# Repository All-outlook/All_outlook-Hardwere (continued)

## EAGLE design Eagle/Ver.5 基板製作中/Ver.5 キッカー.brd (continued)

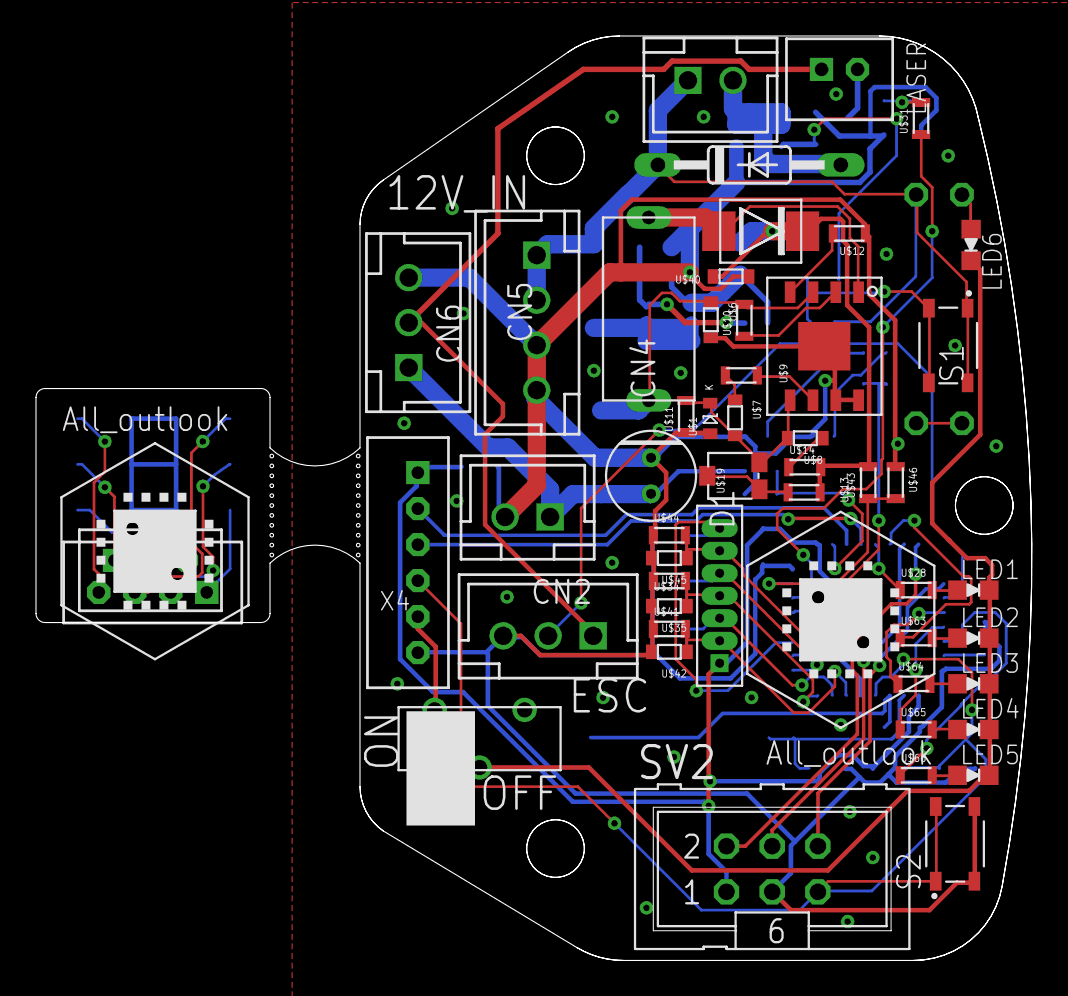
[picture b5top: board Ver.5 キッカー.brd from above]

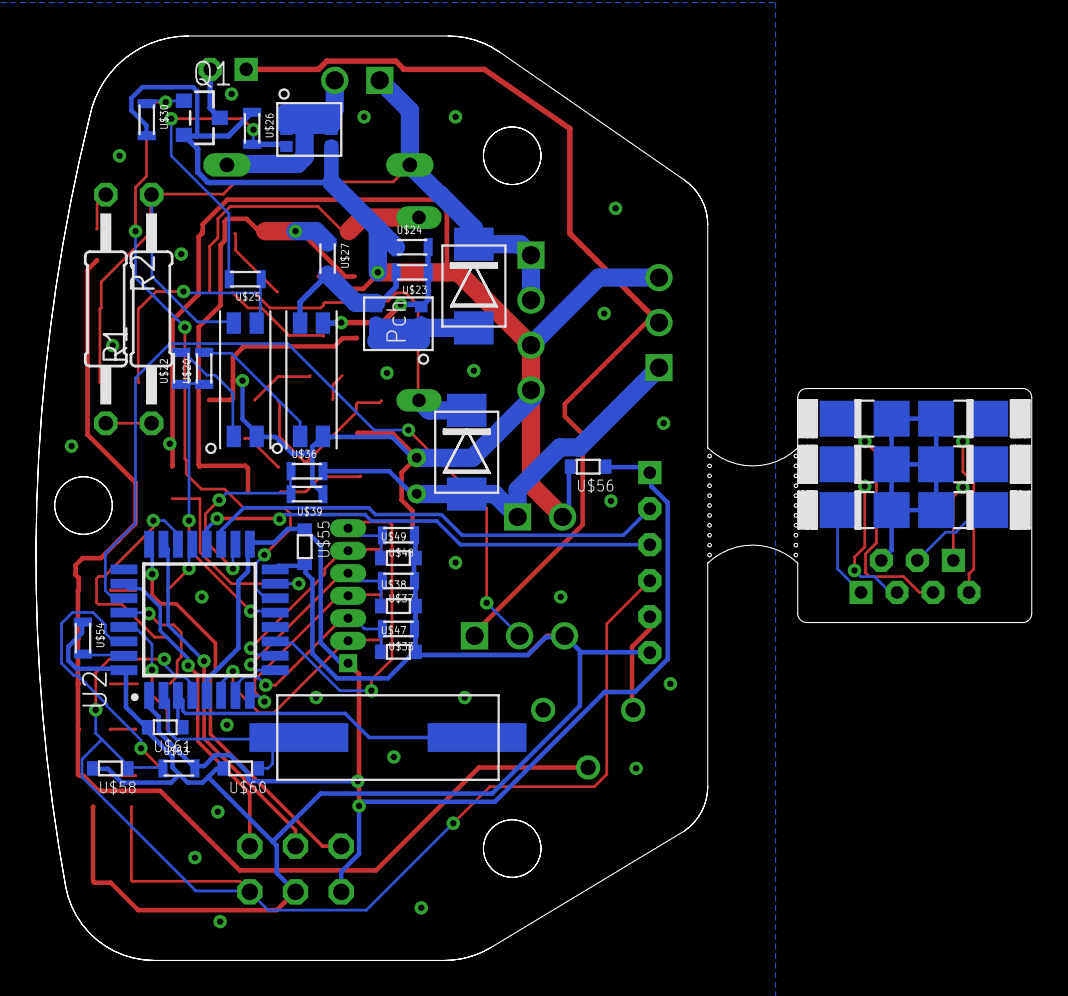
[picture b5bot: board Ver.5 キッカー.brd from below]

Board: 2 copper layers, 55.3 x 51.4 mm, 93 parts (34 on the bottom side), 66 nets.

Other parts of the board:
U$32: ALL

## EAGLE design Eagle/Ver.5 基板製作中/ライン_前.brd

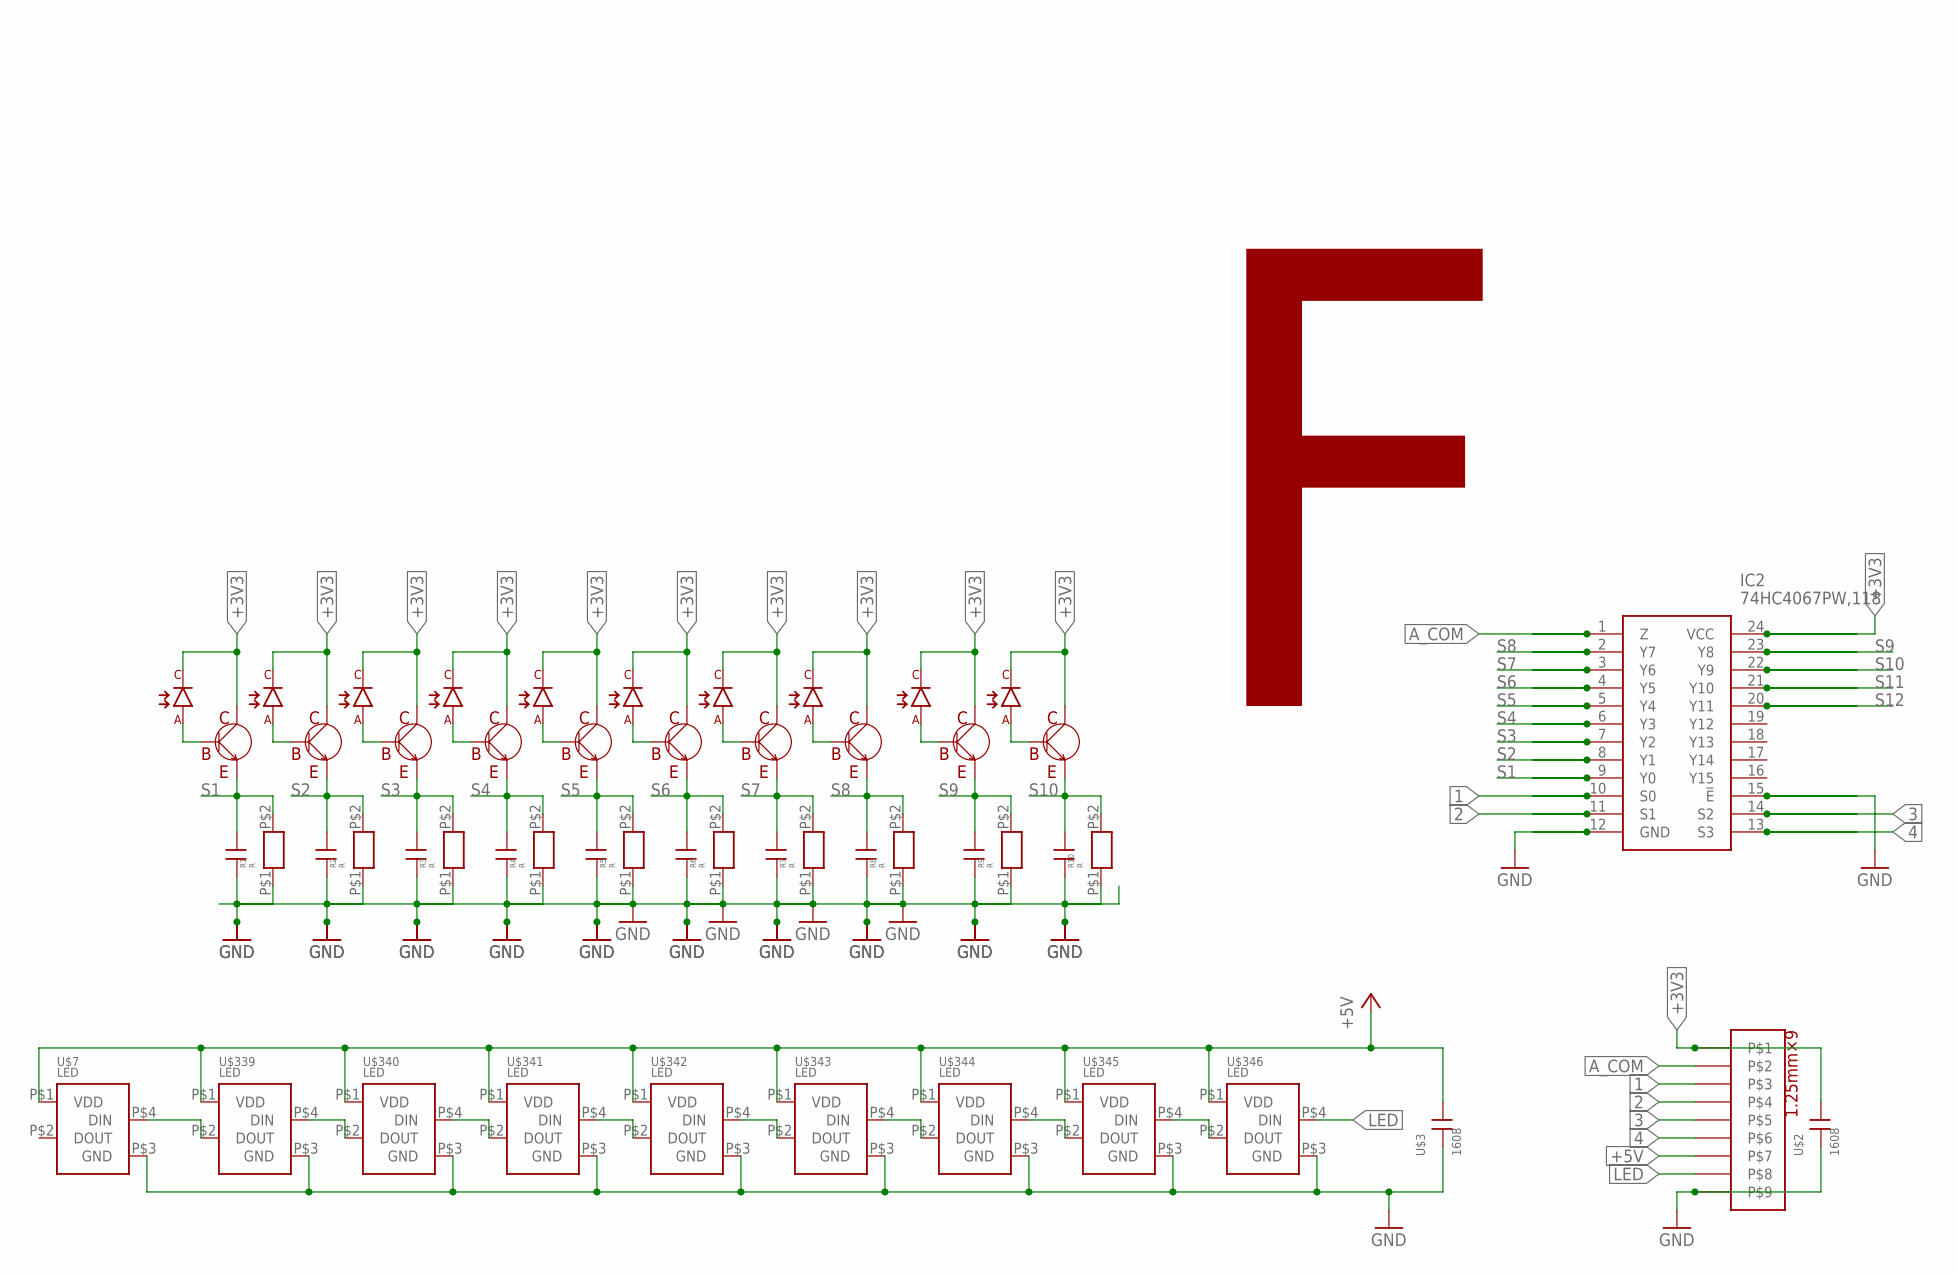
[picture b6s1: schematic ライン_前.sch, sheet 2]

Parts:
C1, C2, C3, C4, C5, C6, C7, C8, C9, C10: 1608; CON
IC2: 74HC4067PW,118; SOP65P640X110-24N
R1, R2, R3, R4, R5, R6, R7, R8, R9, R10: R; 1608
U$1: 1MMCON
U$2, U$3: 1608; CON
U$7, U$339, U$340, U$341, U$342, U$343, U$344, U$345, U$346: LED
U$17, U$19, U$21, U$23, U$25, U$27, U$29, U$31, U$53, U$55: 2CS2712; TRANS_SSM3J325F,LF
U$18, U$20, U$22, U$24, U$26, U$28, U$30, U$32, U$54, U$56: フォトダイオード

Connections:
1: IC2.10 (S0), U$1.P$3
2: IC2.11 (S1), U$1.P$4
3: IC2.14 (S2), U$1.P$5
4: IC2.13 (S3), U$1.P$6
+3V3: IC2.24 (VCC), U$1.P$1, U$2.P$1 (1), U$17.C, U$18.C, U$19.C, U$20.C, U$21.C, U$22.C, U$23.C, U$24.C, U$25.C, U$26.C, U$27.C, U$28.C, U$29.C, U$30.C, U$31.C, U$32.C, U$53.C, U$54.C, U$55.C, U$56.C
+5V: U$1.P$7, U$3.P$1 (1), U$7.P$1 (VDD), U$339.P$1 (VDD), U$340.P$1 (VDD), U$341.P$1 (VDD), U$342.P$1 (VDD), U$343.P$1 (VDD), U$344.P$1 (VDD), U$345.P$1 (VDD), U$346.P$1 (VDD)
A_COM: IC2.1 (Z), U$1.P$2
GND: C1.P$2 (2), C2.P$2 (2), C3.P$2 (2), C4.P$2 (2), C5.P$2 (2), C6.P$2 (2), C7.P$2 (2), C8.P$2 (2), C9.P$2 (2), C10.P$2 (2), IC2.12 (GND), IC2.15 (!E), R1.P$1, R2.P$1, R3.P$1, R4.P$1, R5.P$1, R6.P$1, R7.P$1, R8.P$1, R9.P$1, R10.P$1, U$1.P$9, U$2.P$2 (2), U$3.P$2 (2), U$7.P$3 (GND), U$339.P$3 (GND), U$340.P$3 (GND), U$341.P$3 (GND), U$342.P$3 (GND), U$343.P$3 (GND), U$344.P$3 (GND), U$345.P$3 (GND), U$346.P$3 (GND)
LED: U$1.P$8, U$346.P$4 (DIN)
unnamed: U$7.P$4 (DIN), U$339.P$2 (DOUT)
unnamed: U$17.B, U$18.A
unnamed: U$19.B, U$20.A
unnamed: U$21.B, U$22.A
unnamed: U$23.B, U$24.A
unnamed: U$25.B, U$26.A
unnamed: U$27.B, U$28.A
unnamed: U$29.B, U$30.A
unnamed: U$31.B, U$32.A
unnamed: U$53.B, U$54.A
unnamed: U$55.B, U$56.A
unnamed: U$339.P$4 (DIN), U$340.P$2 (DOUT)
unnamed: U$340.P$4 (DIN), U$341.P$2 (DOUT)
unnamed: U$343.P$4 (DIN), U$344.P$2 (DOUT)
unnamed: U$344.P$4 (DIN), U$345.P$2 (DOUT)
unnamed: U$345.P$4 (DIN), U$346.P$2 (DOUT)
unnamed: U$341.P$4 (DIN), U$342.P$2 (DOUT)
unnamed: U$342.P$4 (DIN), U$343.P$2 (DOUT)
S1: C1.P$1 (1), IC2.9 (Y0), R1.P$2, U$17.E
S2: C2.P$1 (1), IC2.8 (Y1), R2.P$2, U$19.E
S3: C3.P$1 (1), IC2.7 (Y2), R3.P$2, U$21.E
S4: C4.P$1 (1), IC2.6 (Y3), R4.P$2, U$23.E
S5: C5.P$1 (1), IC2.5 (Y4), R5.P$2, U$25.E
S6: C6.P$1 (1), IC2.4 (Y5), R6.P$2, U$27.E
S7: C7.P$1 (1), IC2.3 (Y6), R7.P$2, U$29.E
S8: C8.P$1 (1), IC2.2 (Y7), R8.P$2, U$31.E
S9: C9.P$1 (1), IC2.23 (Y8), R9.P$2, U$53.E
S10: C10.P$1 (1), IC2.22 (Y9), R10.P$2, U$55.E
S11: IC2.21 (Y10)
S12: IC2.20 (Y11)

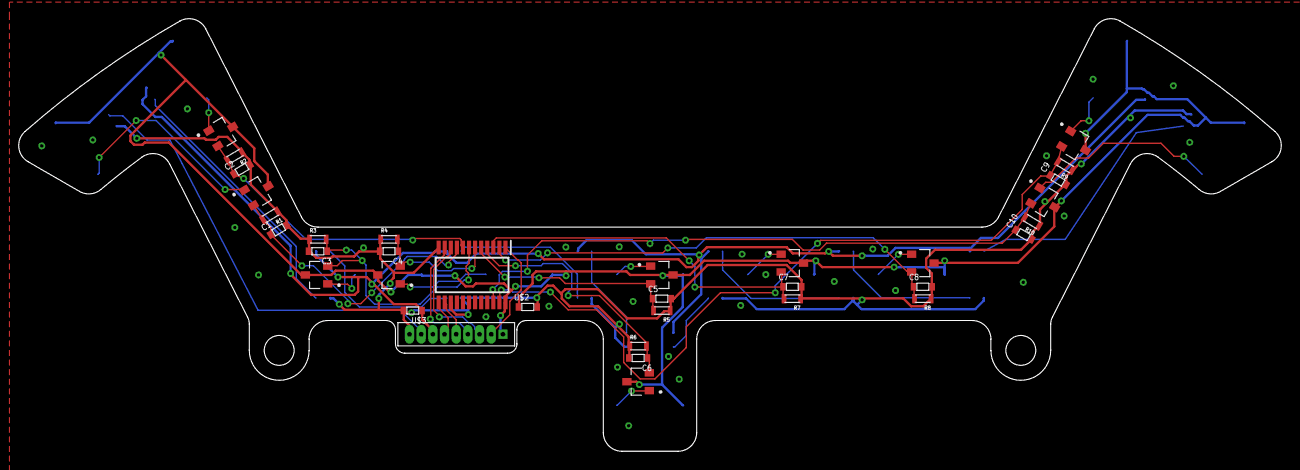
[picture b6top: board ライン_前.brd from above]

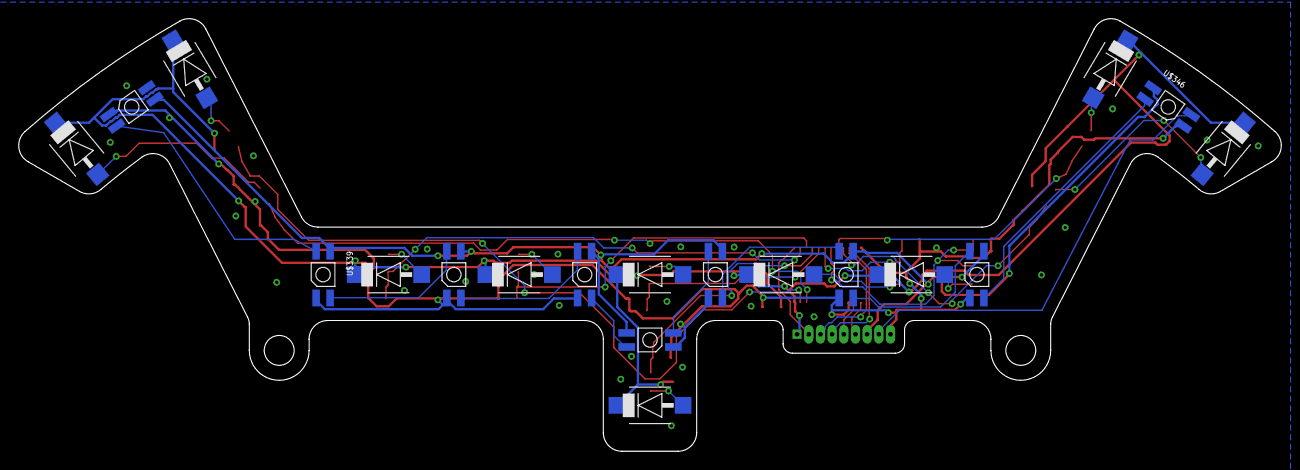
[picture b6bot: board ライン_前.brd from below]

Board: 2 copper layers, 135.2 x 46.3 mm, 53 parts (19 on the bottom side), 37 nets.
